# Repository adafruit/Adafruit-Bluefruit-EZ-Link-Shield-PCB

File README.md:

## Adafruit Bluefruit EZ Link Shield PCB
<a href="http://www.adafruit.com/products/1628"><br/>
Click here to see this in the Adafruit shop</a>

**Note: Discontinued - this product is currently undergoing a revision and will be available again soon!**

The Bluefruit EZ-Link shield is a regular 'SPP' serial link client device, that can pair with any computer or tablet and appear as a serial/COM port (except iOS as iOS does not permit SPP pairing). But here is where it gets exciting: unlike any other BT module, the EZ-Link can automatically detect and change the serial baud rate. That means if you open up the COM port on your computer at 9600 baud, the output is 9600, 57600? 57600. Yep even 2400. All the most common baud rates are supported: 2400, 4800, 9600, 19200, 38400, 57600, 115200 and 230400. You never have to configure or customize the module by hand - it all happens completely automatically inside the RF module.

PCB files for the Adafruit Bluefruit EZ-Link Shield. The format is EagleCAD schematic and board layout
- https://www.adafruit.com/product/1628

### License

Adafruit invests time and resources providing this open source design, please support Adafruit and open-source hardware by purchasing products from [Adafruit](https://www.adafruit.com)!

All text above must be included in any redistribution

Designed by Limor Fried/Ladyada for Adafruit Industries.
Creative Commons Attribution/Share-Alike, all text above must be included in any redistribution. 
See license.txt for additional information.

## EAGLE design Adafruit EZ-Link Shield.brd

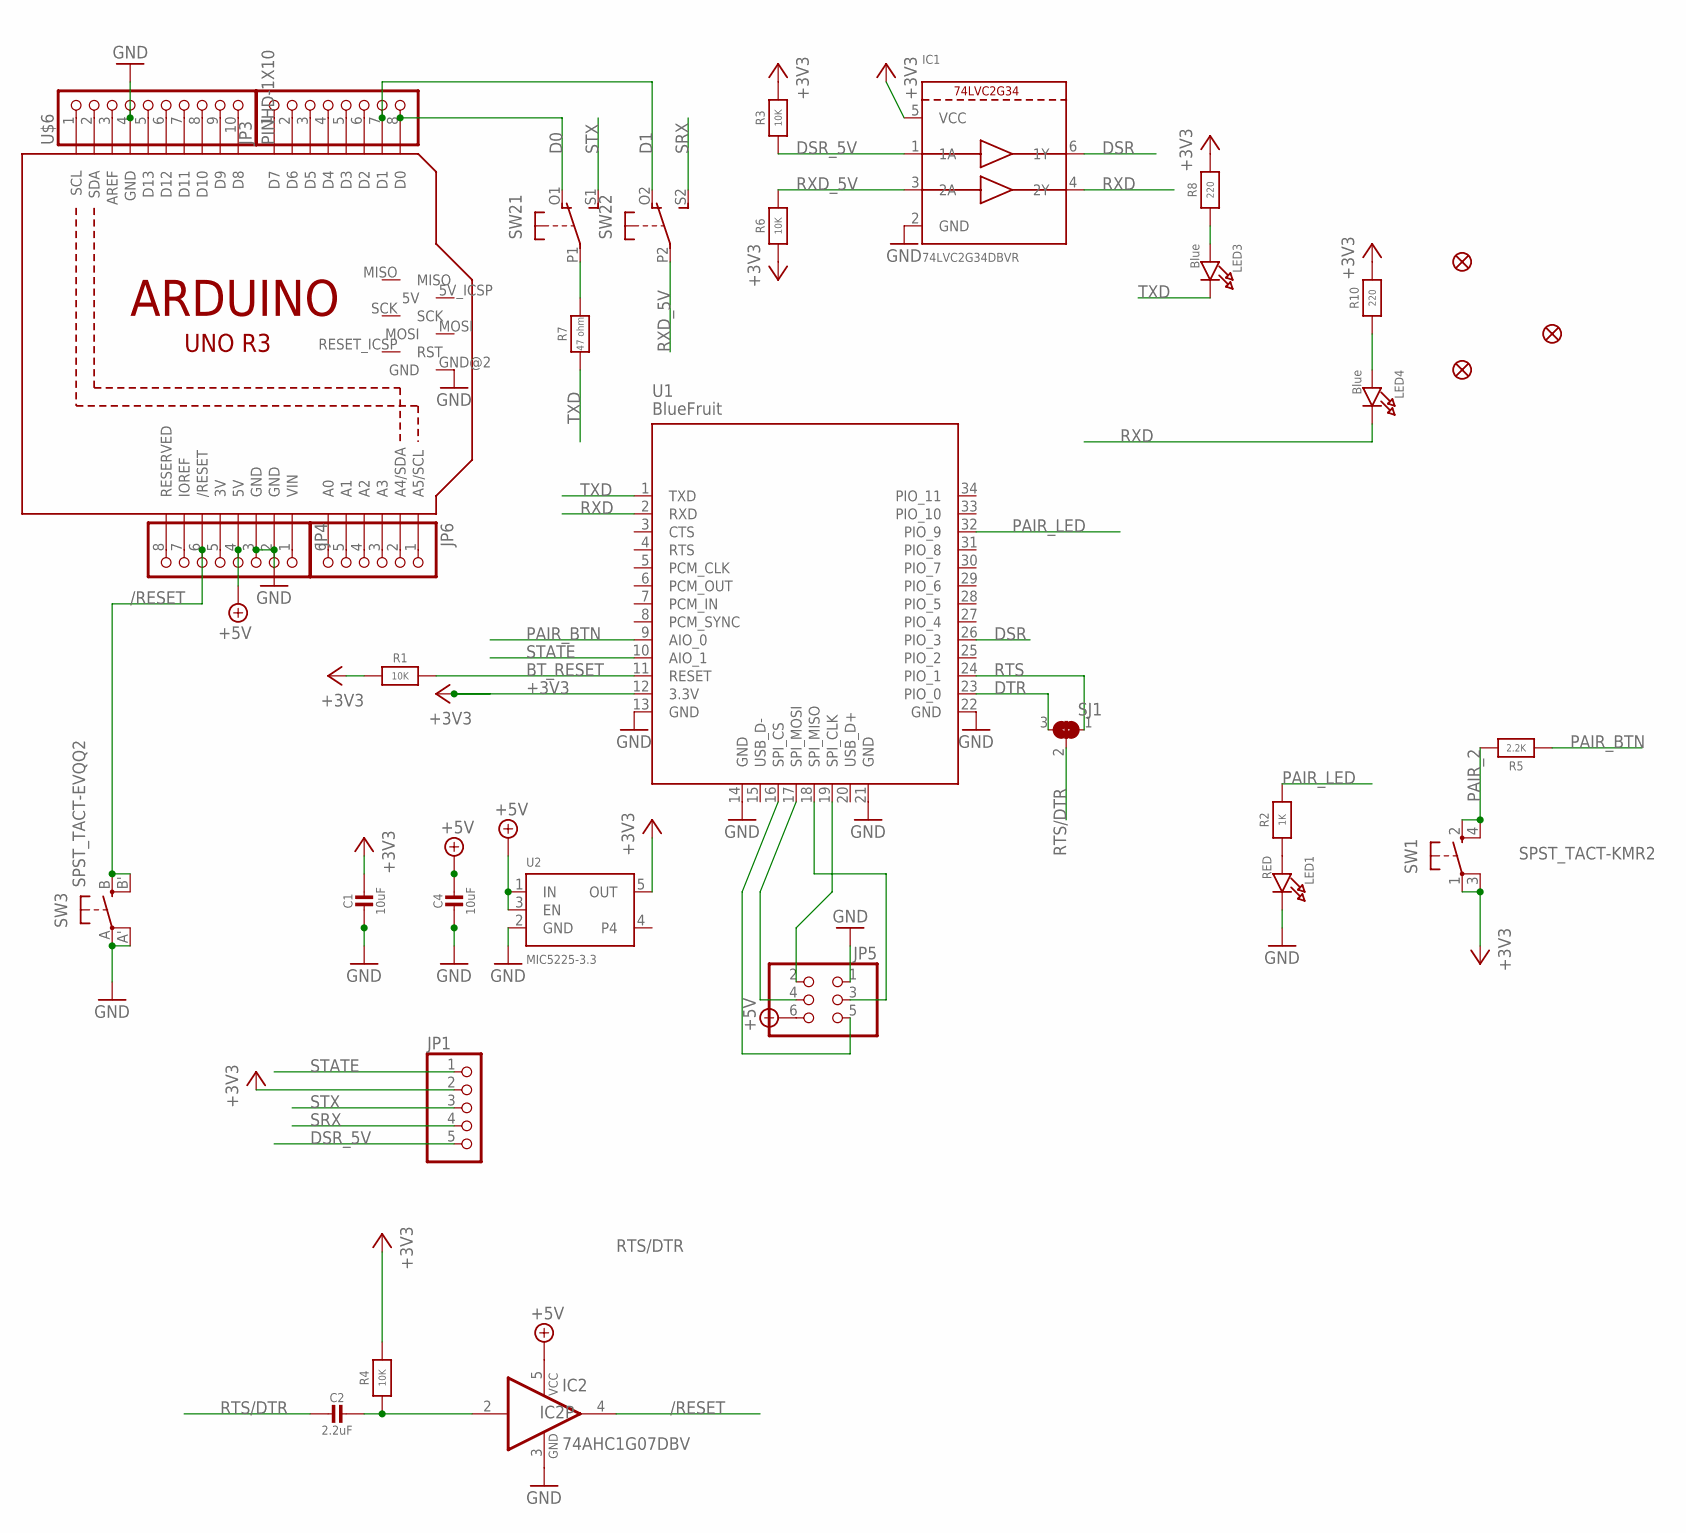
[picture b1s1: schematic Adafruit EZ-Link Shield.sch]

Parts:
C1, C4: 10uF; 0805-NO
C2: 2.2uF; 0805-NO
FID1, FID2, FID3: FIDUCIAL""; FIDUCIAL_1MM
IC1: 74LVC2G34DBVR; SOT23-6
IC2: 74AHC1G07DBV; SOT23-5
JP1: HEADER-1X570MIL; 1X05_ROUND_70
JP3, JP4: PINHD-1X8BIG; 1X08-BIG
JP5: HEADER-2X3; 2X03_ROUND_70MIL
JP6: PINHD-1X6B; 1X06-BIG
LED1: RED; CHIPLED_0805_NOOUTLINE
LED3, LED4: Blue; CHIPLED_0805_NOOUTLINE
R1, R4: 10K; 0805-NO
R2: 1K; 0805-NO
R3, R6: 10K; _0805MP
R5: 2.2K; 0805-NO
R7: 47 ohm; 0805-NO
R8, R10: 220; 0805-NO
SJ1: SOLDERJUMPER_2WAY; SOLDERJUMPER_2WAY_OPEN_NOPASTE
SW1: SPST_TACT-KMR2; KMR2
SW2: DPDT-EG1390; EG1390
SW3: SPST_TACT-EVQQ2; EVQ-Q2
U1: BlueFruit; BLUETOOTH_MODULE
U2: MIC5225-3.3; SOT23-5
U$5: ARDUINO_R3_ICSP; ARDUINOR3_ICSP
U$6: PINHD-1X10; 1X10-BIG

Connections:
+3V3: C1.1, IC1.5 (VCC), JP1.2, R1.1, R3.2, R4.2, R6.1, R8.2, R10.2, SW1.1, SW1.3 (P1), U1.12 (3.3V), U2.5 (OUT)
+5V: C4.1, IC2.5 (VCC), JP4.4, JP5.6, U2.1 (IN), U2.3 (EN), U$5.5V
/RESET: IC2.4 (O), JP4.6, SW3.B (S), SW3.B' (S1), U$5.RESET (/RESET)
BT_RESET: R1.2, U1.11 (RESET)
D0: JP3.8, SW2.O1 (O), U$5.D0
D1: JP3.7, SW2.O2 (O), U$5.D1
DSR: IC1.6 (1Y), U1.26 (PIO_3)
DSR_5V: IC1.1 (1A), JP1.5, R3.1
DTR: SJ1.3, U1.23 (PIO_0)
GND: C1.2, C4.2, IC1.2 (GND), IC2.3 (GND), JP4.2, JP4.3, JP5.1, LED1.C, SW3.A, SW3.A' (P1), U1.13 (GND), U1.14 (GND), U1.21 (GND), U1.22 (GND), U2.2 (GND), U$5.GND, U$5.GND@1 (GND), U$5.GND@2 (GND), U$5.GND@3 (GND), U$6.4
unnamed: C2.1, IC2.2 (I), R4.1
unnamed: LED1.A, R2.1
unnamed: R7.2, SW2.P1
unnamed: JP3.1, U$5.D7
unnamed: JP3.2, U$5.D6
unnamed: LED3.A, R8.1
unnamed: JP3.3, U$5.D5
unnamed: JP3.4, U$5.D4
unnamed: LED4.A, R10.1
unnamed: JP3.5, U$5.D3
unnamed: JP3.6, U$5.D2
unnamed: JP4.1, U$5.VIN
unnamed: JP4.5, U$5.3V
unnamed: JP4.7, U$5.IOREF
unnamed: JP4.8, U$5.RESERVED
unnamed: JP6.1, U$5.A5 (A5/SCL)
unnamed: JP6.2, U$5.A4 (A4/SDA)
unnamed: JP6.3, U$5.A3
unnamed: JP6.4, U$5.A2
unnamed: JP6.5, U$5.A1
unnamed: JP6.6, U$5.A0
unnamed: U$5.SCL, U$6.1
unnamed: U$5.SDA, U$6.2
unnamed: U$5.AREF, U$6.3
unnamed: U$5.D13, U$6.5
unnamed: U$5.D12, U$6.6
unnamed: U$5.D11, U$6.7
unnamed: U$5.D10, U$6.8
unnamed: U$5.D9, U$6.9
unnamed: U$5.D8, U$6.10
PAIR_2: R5.2, SW1.2 (S), SW1.4 (S1)
PAIR_BTN: R5.1, U1.9 (AIO_0)
PAIR_LED: R2.2, U1.32 (PIO_9)
RTS: SJ1.1, U1.24 (PIO_1)
RTS/DTR: C2.2, SJ1.2
RXD: IC1.4 (2Y), LED4.C, U1.2 (RXD)
RXD_5V: IC1.3 (2A), R6.2, SW2.P2
SPI_CLK: JP5.2, U1.19 (SPI_CLK)
SPI_CS: JP5.5, U1.16 (SPI_CS)
SPI_MISO: JP5.3, U1.18 (SPI_MISO)
SPI_MOSI: JP5.4, U1.17 (SPI_MOSI)
SRX: JP1.4, SW2.S2 (S)
STATE: JP1.1, U1.10 (AIO_1)
STX: JP1.3, SW2.S1 (S)
TXD: LED3.C, R7.1, U1.1 (TXD)

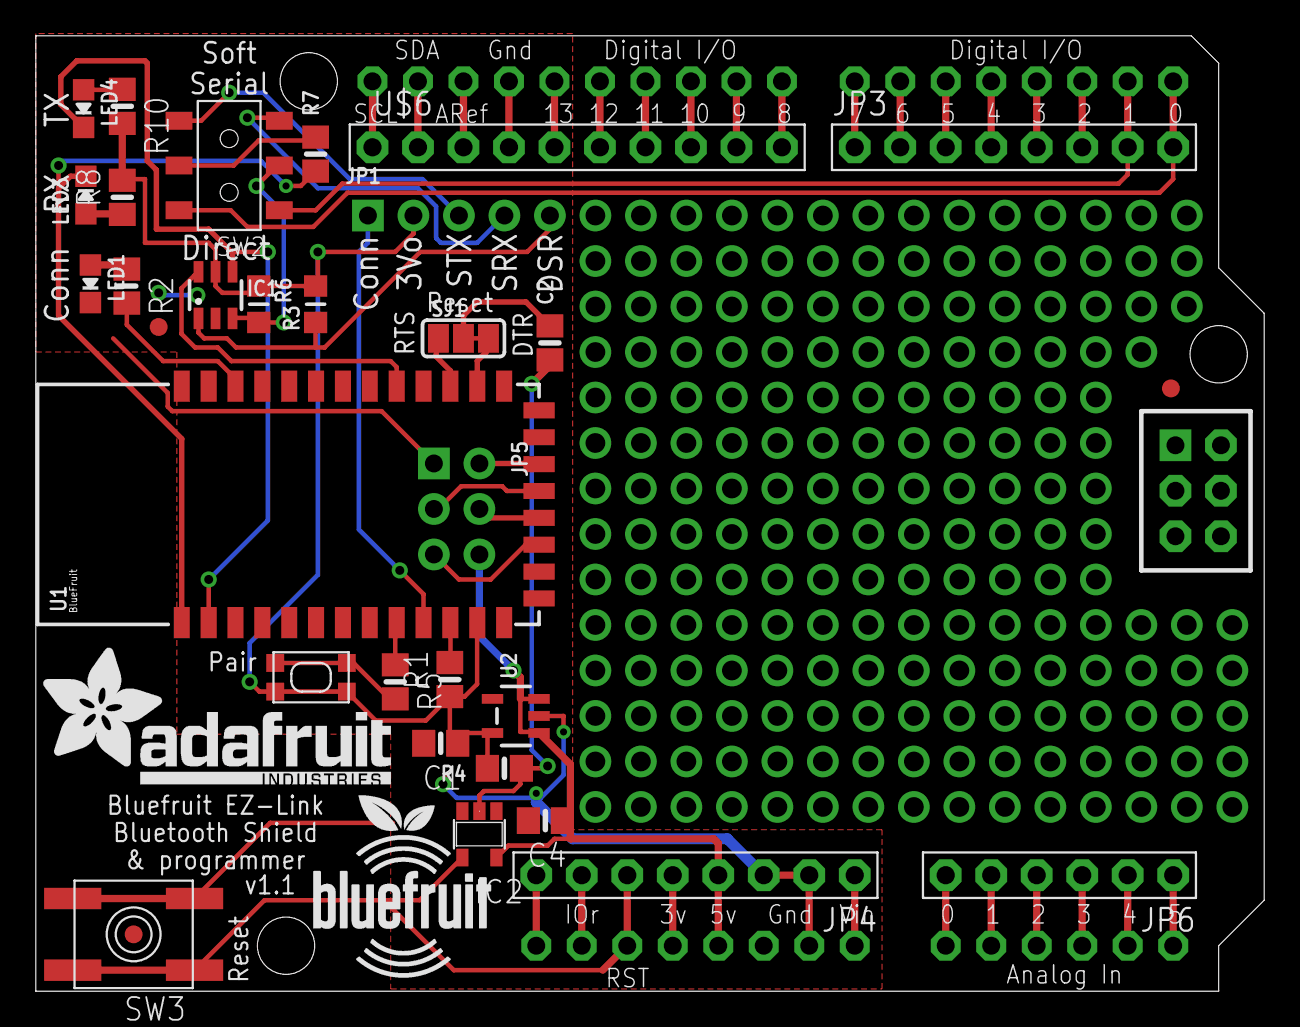
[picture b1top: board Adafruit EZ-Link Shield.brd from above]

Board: 2 copper layers, 68.6 x 53.3 mm, 35 parts (0 on the bottom side), 55 nets.

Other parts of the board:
U$4: BLUEFRUITLOGO_100MM
U$7: ADAFRUIT_TEXT_20MM

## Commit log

2016-08-05 ez-init
